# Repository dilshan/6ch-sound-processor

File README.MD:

# 5.1 channel analog audio processor

This project is a 5.1-channel, analog audio processor based on *PT2322* and [Arduino Nano](https://store.arduino.cc/products/arduino-nano).

[*PT2322*](https://www.alldatasheet.com/datasheet-pdf/pdf/167269/ETC1/PT2322.html) is an inexpensive analog audio processor introduced by [*Princeton Technology Corporation*](http://www.princeton.com.tw/). It contains 6-channel individual channel attenuators, a 3-way tone control system for front-end speakers, and a 3D audio simulation system.

In this design, we combine *PT2322* with *Arduino Nano* and interface it with PC/embedded computing boards through a USB port. Native *GTK* UI application provides to control all functions of the *PT2322* IC.

This audio processing module is an open-source hardware project. All the design files, source codes, and compiled binaries are available in this repository.

- [6ch-sound-fx-arduino](https://github.com/dilshan/6ch-sound-processor/tree/main/6ch-sound-fx-arduino): Source code of the *Arduino Nano* firmware.
- [6ch-sound-fx-controller](https://github.com/dilshan/6ch-sound-processor/tree/main/6ch-sound-fx-controller): Source code of the sound processor control application.
- [kicad-design](https://github.com/dilshan/6ch-sound-processor/tree/main/kicad-design): *KiCAD* 6 schematic and PCB design.

## Assembling the module

The PCB of this module can directly order from the [PCBWay project page](https://www.pcbway.com/project/shareproject/5_1_channel_analog_audio_processor_231ad745.html). Also, the latest Gerber files of this module are available in the [release](https://github.com/dilshan/6ch-sound-processor/releases) section of this repository.

All the required components to assemble this module are in the BOM file at [here](https://github.com/dilshan/6ch-sound-processor/tree/main/kicad-design/6ch-sound-fx-proc-bom.pdf).

The entire assembly process of this module is shown in the below video:

## Compiling source codes

*Arduino Nano* firmware of this project is written using [*PlatformIO*](https://platformio.org/). To compile and install the firmware, use the latest version of [*PlatformIO IDE*](https://platformio.org/platformio-ide).

The sound processor control application is a *GTK* application. *GTK* 3 development packages are required to compile this application. To compile the application, issue the `make` command from the source directory.

```
$ git clone git@github.com:dilshan/6ch-sound-processor.git
$ cd 6ch-sound-processor/6ch-sound-fx-controller/
$ make
```

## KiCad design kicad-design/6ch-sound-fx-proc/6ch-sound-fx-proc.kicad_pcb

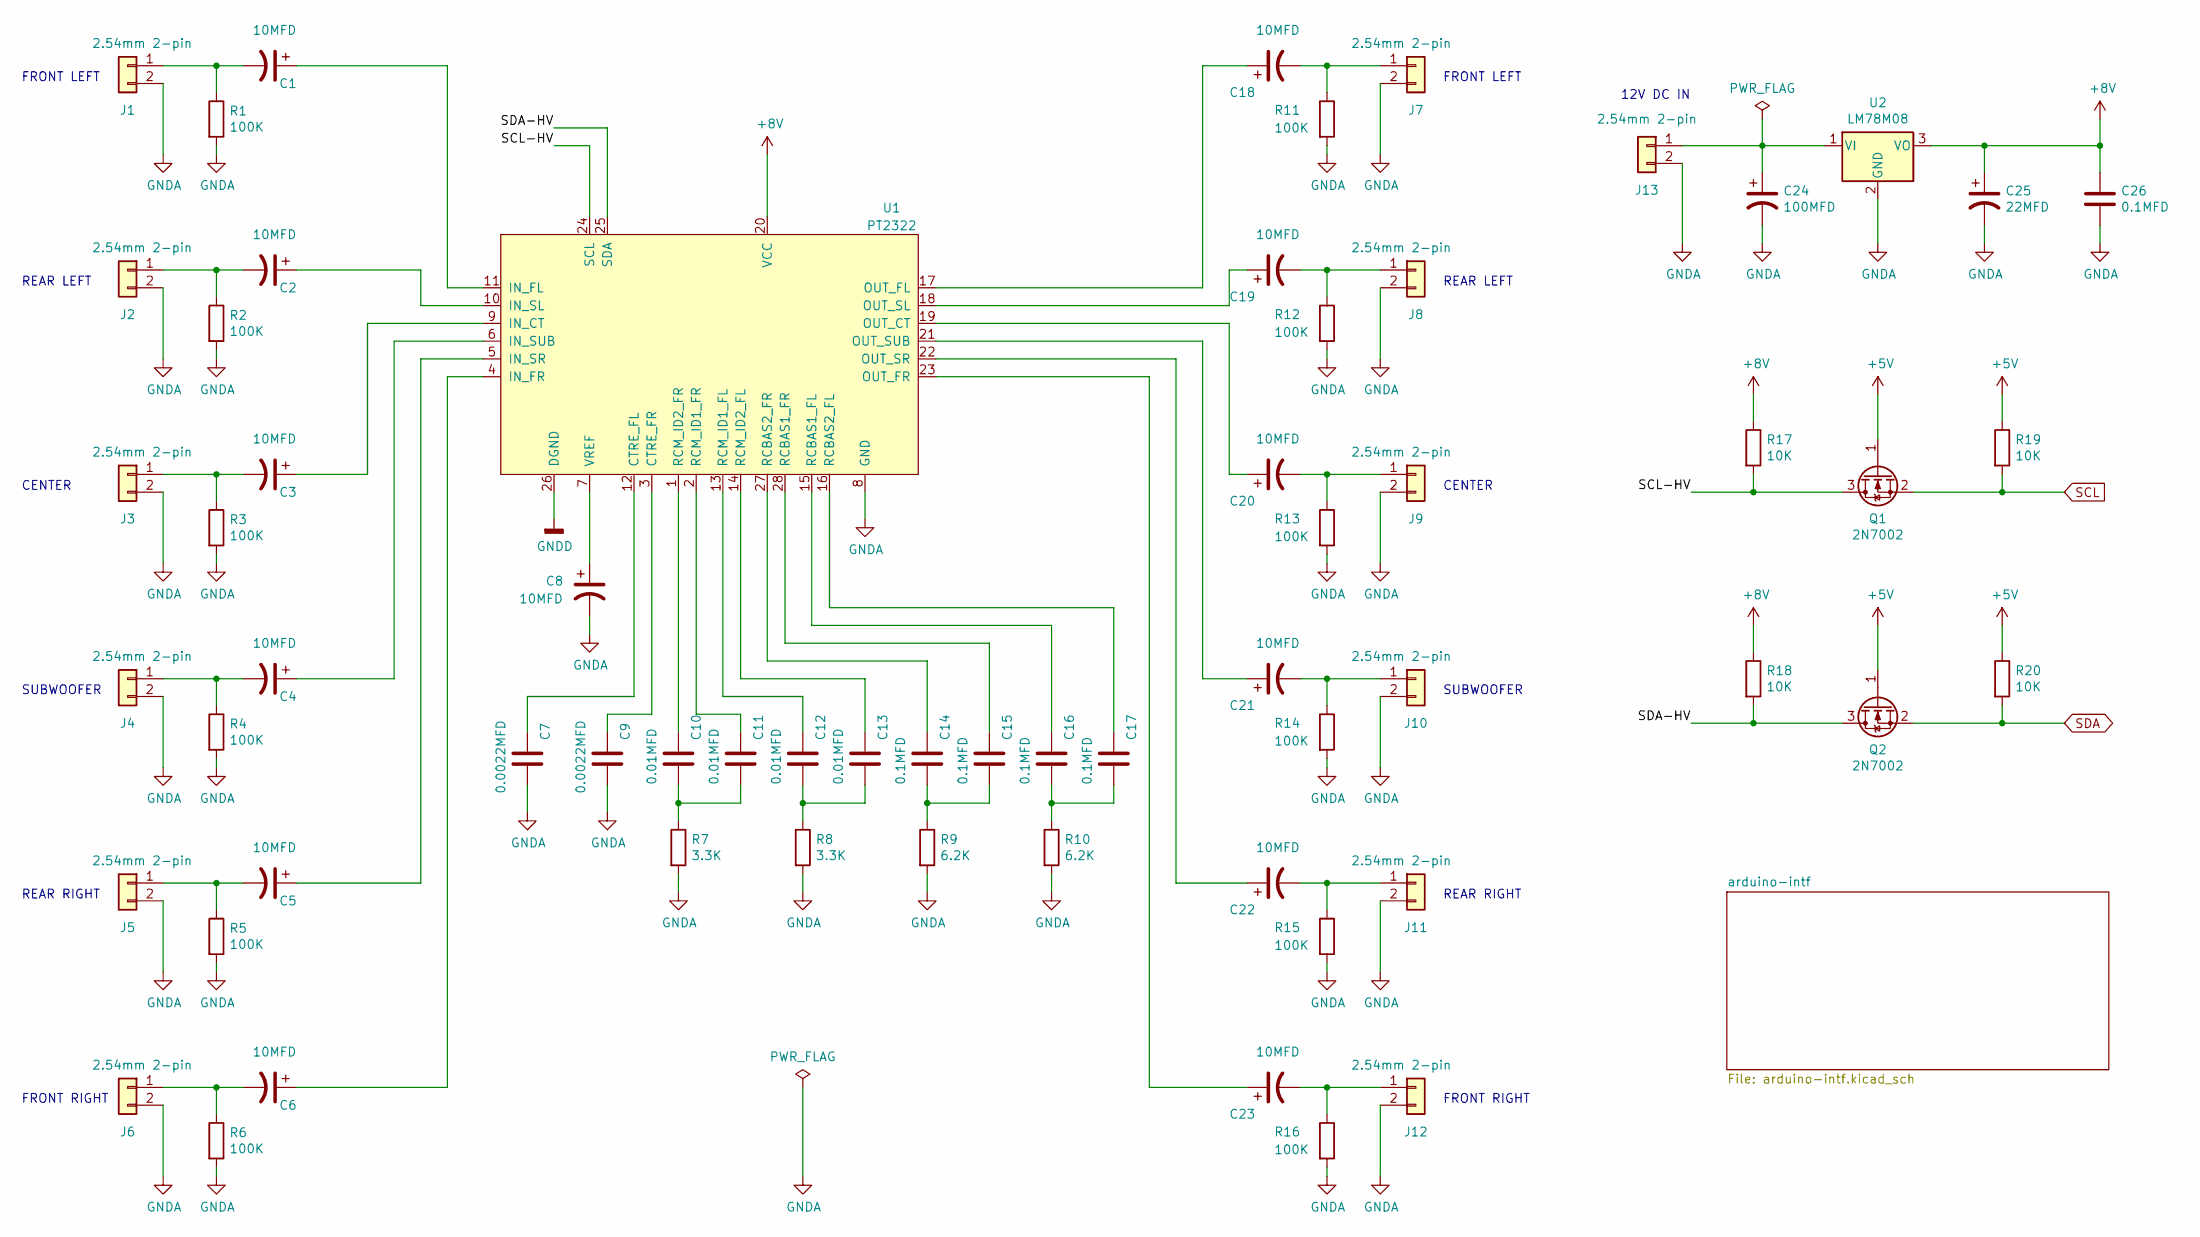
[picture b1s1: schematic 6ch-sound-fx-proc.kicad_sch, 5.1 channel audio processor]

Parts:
C1, C2, C3, C4, C5, C6, C8, C18, C19, C20, C21, C22, C23: 10MFD; CP_Radial_D5.0mm_P2.00mm
C7, C9: 0.0022MFD; C_0805_2012Metric_Pad1.18x1.45mm_HandSolder
C10, C11, C12, C13: 0.01MFD; C_0805_2012Metric_Pad1.18x1.45mm_HandSolder
C14, C15, C16, C17, C26: 0.1MFD; C_0805_2012Metric_Pad1.18x1.45mm_HandSolder
C24: 100MFD; CP_Radial_D6.3mm_P2.50mm
C25: 22MFD; CP_Radial_D5.0mm_P2.00mm
J1, J2, J3, J4, J5, J6, J7, J8, J9, J10, J11, J12: 2.54mm 2-pin; PinHeader_1x02_P2.54mm_Vertical
J13: 2.54mm 2-pin; PhoenixContact_MCV_1,5_2-G-3.5_1x02_P3.50mm_Vertical
Q1, Q2: 2N7002; SOT-23
R1, R2, R3, R4, R5, R6, R11, R12, R13, R14, R15, R16: 100K; R_0805_2012Metric_Pad1.20x1.40mm_HandSolder
R7, R8: 3.3K; R_Axial_DIN0207_L6.3mm_D2.5mm_P10.16mm_Horizontal
R9, R10: 6.2K; R_Axial_DIN0207_L6.3mm_D2.5mm_P10.16mm_Horizontal
R17, R18, R19, R20: 10K; R_0805_2012Metric_Pad1.20x1.40mm_HandSolder
U1: PT2322; SSOP-28_5.3x10.2mm_P0.65mm
U2: LM78M08; TO-252-2

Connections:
+5V: Q1.1 (G), Q2.1 (G), R19.1, R20.1; also elsewhere on the board
+8V: C25.1, C26.1, R17.1, R18.1, U1.20 (VCC), U2.3 (VO)
/SCL-HV: Q1.3 (D), R17.2, U1.24 (SCL)
/SDA-HV: Q2.3 (D), R18.2, U1.25 (SDA)
GNDA: C7.2, C8.2, C9.2, C24.2, C25.2, C26.2, J1.2, J2.2, J3.2, J4.2, J5.2, J6.2, J7.2, J8.2, J9.2, J10.2, J11.2, J12.2, J13.2, R1.2, R2.2, R3.2, R4.2, R5.2, R6.2, R7.2, R8.2, R9.2, R10.2, R11.2, R12.2, R13.2, R14.2, R15.2, R16.2, U1.8 (GND), U2.2 (GND); also elsewhere on the board
GNDD: U1.26 (DGND); also elsewhere on the board
unnamed: C1.1, U1.11 (IN_FL)
unnamed: C1.2, J1.1, R1.1
unnamed: C2.1, U1.10 (IN_SL)
unnamed: C2.2, J2.1, R2.1
unnamed: C3.1, U1.9 (IN_CT)
unnamed: C3.2, J3.1, R3.1
unnamed: C4.1, U1.6 (IN_SUB)
unnamed: C4.2, J4.1, R4.1
unnamed: C5.1, U1.5 (IN_SR)
unnamed: C5.2, J5.1, R5.1
unnamed: C6.1, U1.4 (IN_FR)
unnamed: C6.2, J6.1, R6.1
unnamed: C7.1, U1.12 (CTRE_FL)
unnamed: C8.1, U1.7 (VREF)
unnamed: C9.1, U1.3 (CTRE_FR)
unnamed: C10.1, U1.1 (RCM_ID2_FR)
unnamed: C10.2, C11.2, R7.1
unnamed: C11.1, U1.2 (RCM_ID1_FR)
unnamed: C12.1, U1.13 (RCM_ID1_FL)
unnamed: C12.2, C13.2, R8.1
unnamed: C13.1, U1.14 (RCM_ID2_FL)
unnamed: C14.1, U1.27 (RCBAS2_FR)
unnamed: C14.2, C15.2, R9.1
unnamed: C15.1, U1.28 (RCBAS1_FR)
unnamed: C16.1, U1.15 (RCBAS1_FL)
unnamed: C16.2, C17.2, R10.1
unnamed: C17.1, U1.16 (RCBAS2_FL)
unnamed: C18.1, U1.17 (OUT_FL)
unnamed: C18.2, J7.1, R11.1
unnamed: C19.1, U1.18 (OUT_SL)
unnamed: C19.2, J8.1, R12.1
unnamed: C20.1, U1.19 (OUT_CT)
unnamed: C20.2, J9.1, R13.1
unnamed: C21.1, U1.21 (OUT_SUB)
unnamed: C21.2, J10.1, R14.1
unnamed: C22.1, U1.22 (OUT_SR)
unnamed: C22.2, J11.1, R15.1
unnamed: C23.1, U1.23 (OUT_FR)
unnamed: C23.2, J12.1, R16.1
unnamed: C24.1, J13.1, U2.1 (VI)
SCL: Q1.2 (S), R19.2; also elsewhere on the board
SDA: Q2.2 (S), R20.2; also elsewhere on the board

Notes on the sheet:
SUBWOOFER
FRONT LEFT
FRONT RIGHT
REAR LEFT
REAR RIGHT
CENTER
12V DC IN

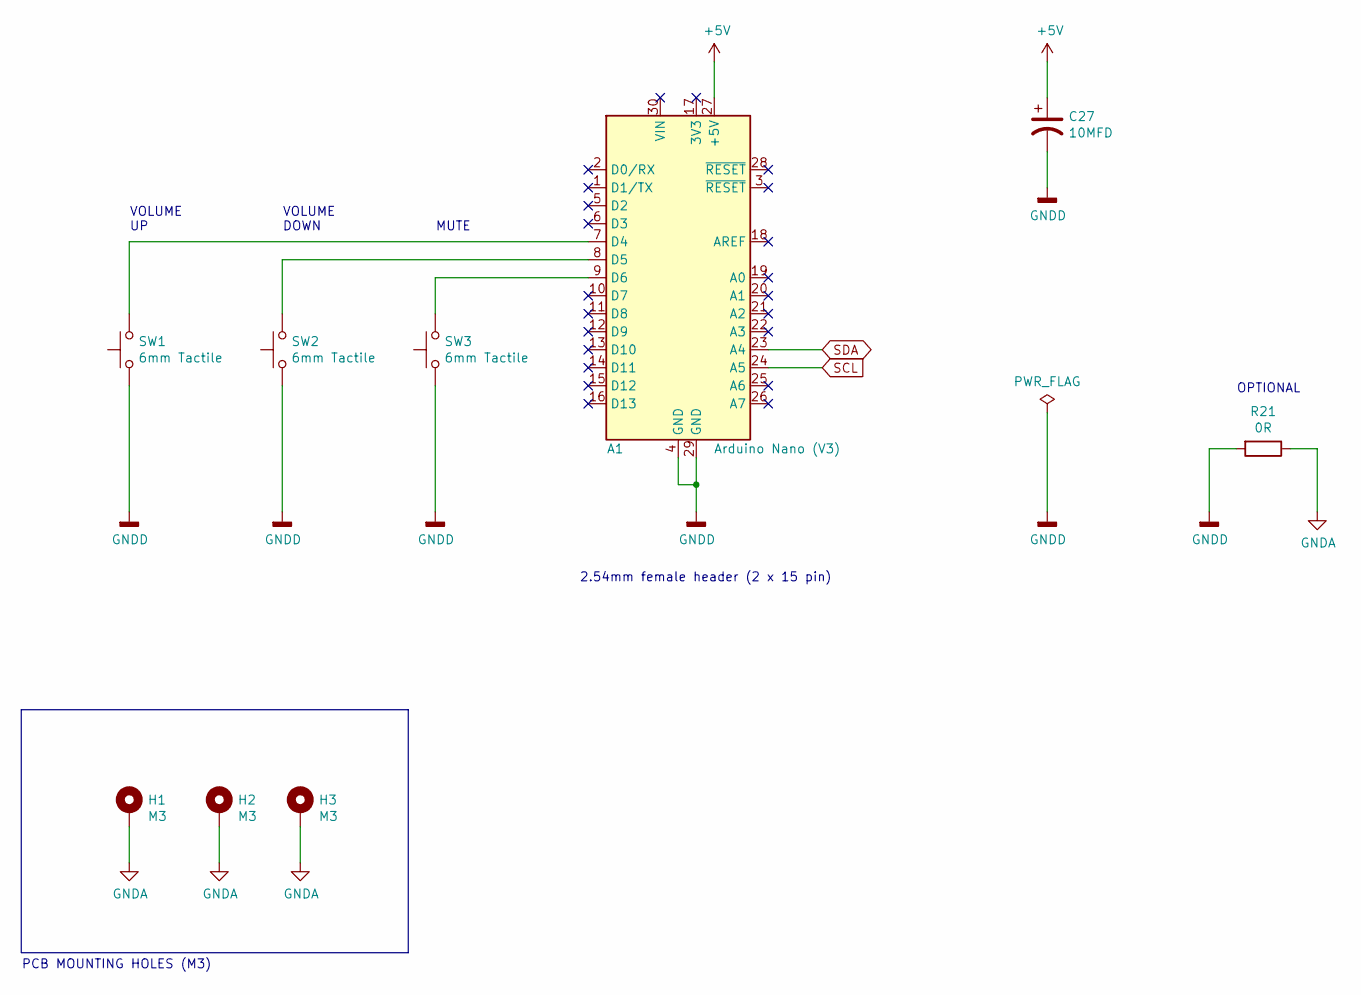
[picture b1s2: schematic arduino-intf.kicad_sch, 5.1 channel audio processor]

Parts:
A1: Arduino Nano (V3); Arduino_Nano
C27: 10MFD; CP_Radial_D5.0mm_P2.00mm
H1, H2, H3: M3; MountingHole_3.2mm_M3_Pad
R21: 0R; R_0805_2012Metric_Pad1.20x1.40mm_HandSolder
SW1, SW2, SW3: 6mm Tactile; SW_PUSH_6mm

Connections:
+5V: A1.27 (+5V), C27.1; also elsewhere on the board
GNDA: H1.1, H2.1, H3.1, R21.1; also elsewhere on the board
GNDD: A1.4 (GND), A1.29 (GND), C27.2, R21.2, SW1.1, SW2.1, SW3.1; also elsewhere on the board
unnamed: A1.7 (D4), SW1.2
unnamed: A1.8 (D5), SW2.2
unnamed: A1.9 (D6), SW3.2
SCL: A1.24 (A5); also elsewhere on the board
SDA: A1.23 (A4); also elsewhere on the board

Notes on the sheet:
2.54mm female header (2 x 15 pin)
VOLUME DOWN
PCB MOUNTING HOLES (M3)
VOLUME UP
OPTIONAL
MUTE

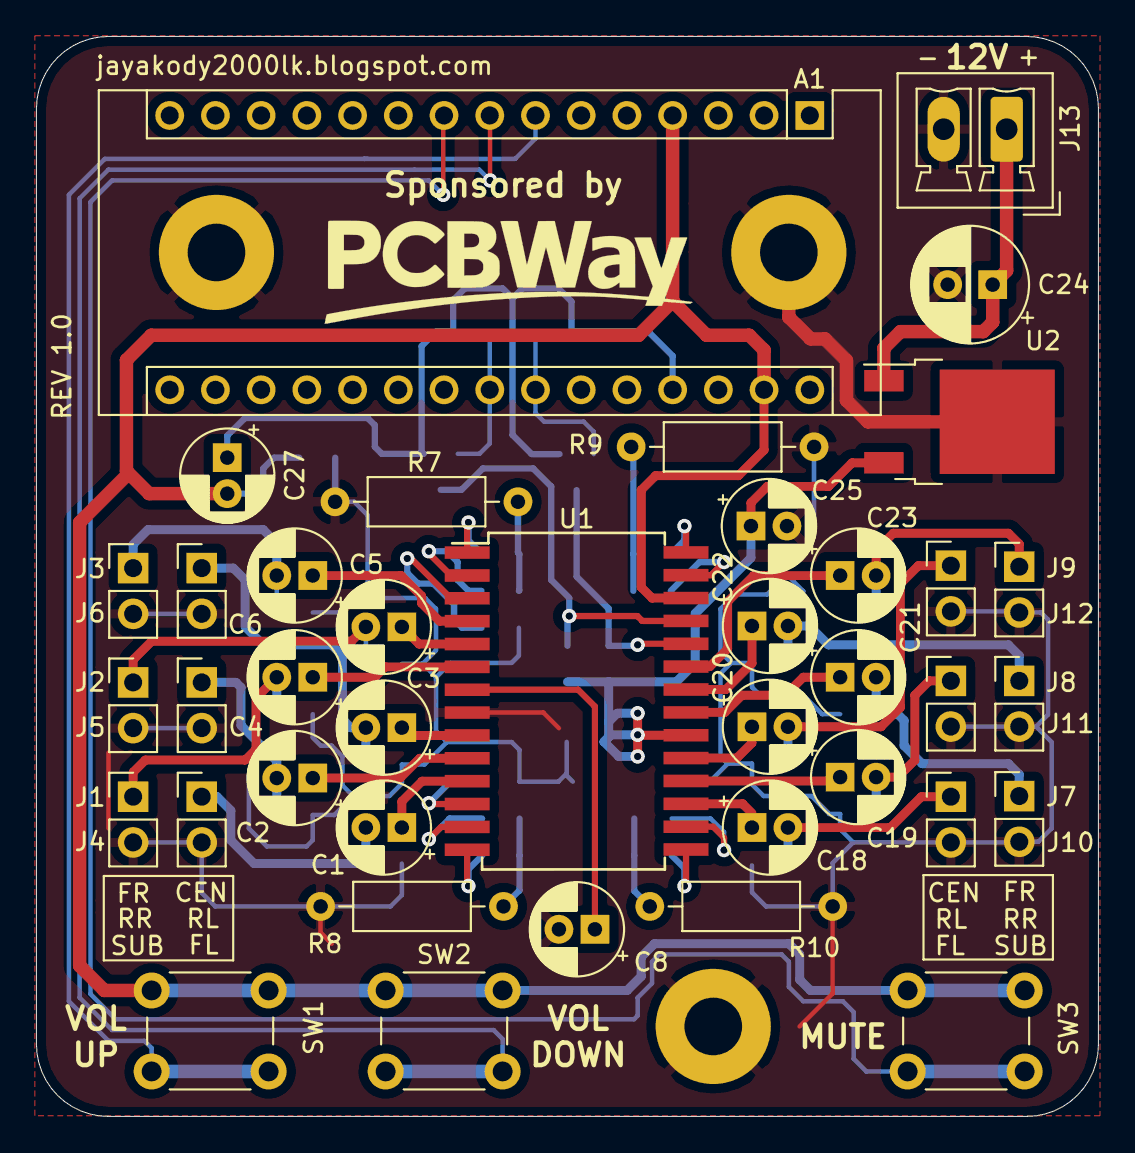
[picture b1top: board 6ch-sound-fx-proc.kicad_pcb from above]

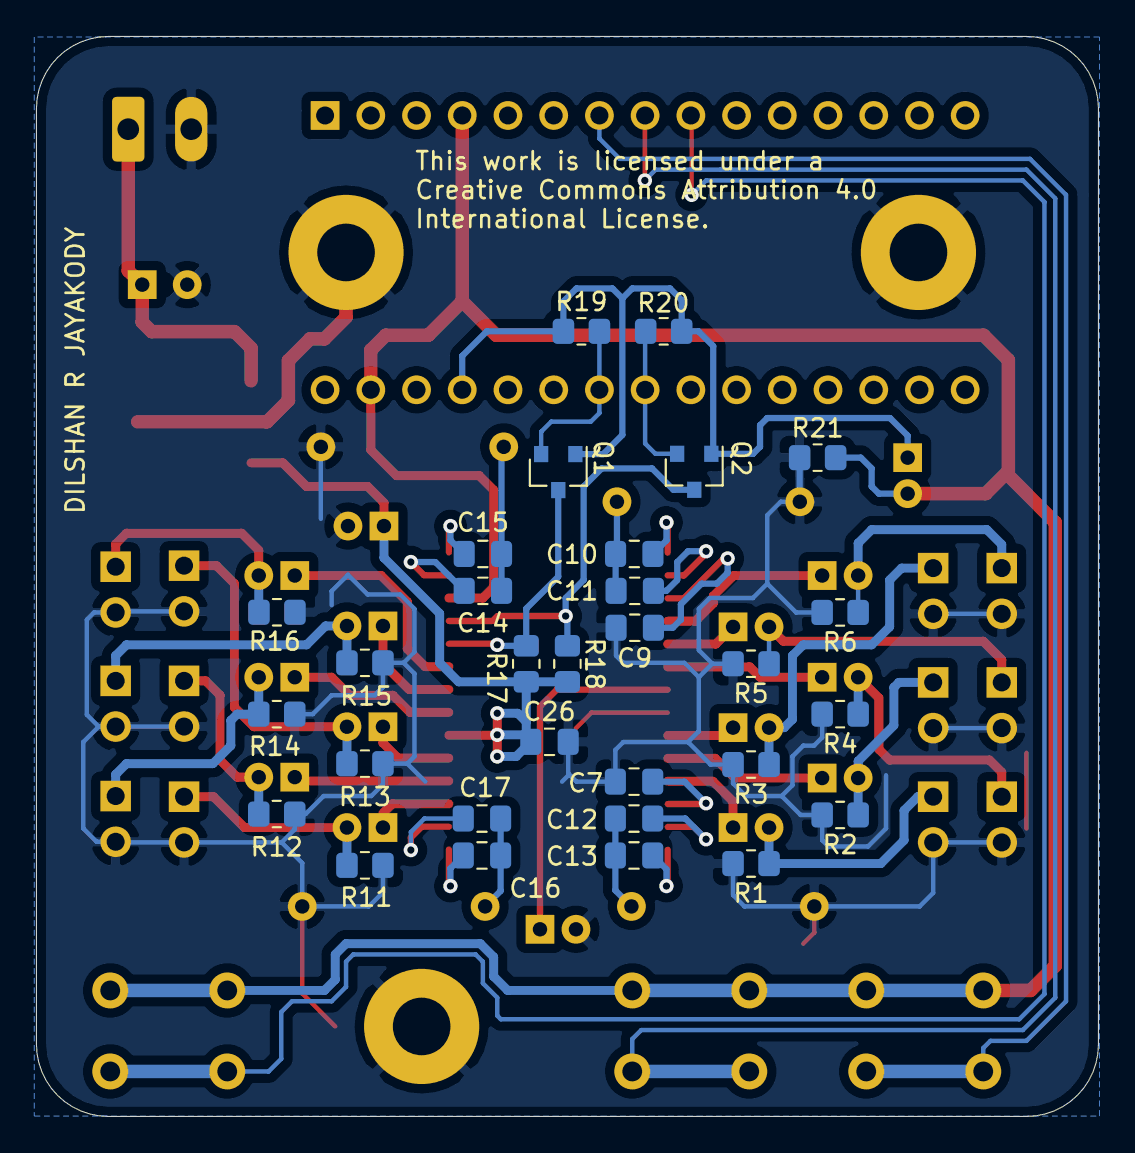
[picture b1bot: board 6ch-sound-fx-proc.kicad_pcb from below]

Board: 2 copper layers, 59.0 x 60.0 mm, 72 parts (30 on the bottom side), 51 nets.

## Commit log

2022-10-21 Add software license file.
2022-10-21 Initial commit of source files and design files.
2022-10-21 Add missing resource definition file.
2022-10-24 Update version information of the schematic and PCB design.
2022-10-24 Add BOM file and readme.md file.
2022-10-24 Add PDF version of the schematic.
2022-10-24 Add image of the prototype project and application screenshot.
2022-10-24 Update resolution of the assembled PCB image.
2022-10-24 Add board and application images to the readme.md file.
2022-10-24 Change BOM file name.
2022-10-24 Fix compilation issues with GCC 9.3.
2022-10-24 Fix UI issues in serial connection path.
2022-10-24 Add YouTube video link to the readme.md file.
2022-10-24 Add PCBWay project page URL.

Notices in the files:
kicad-design/6ch-sound-fx-proc/6ch-sound-fx-proc.kicad_pcb:
This work is licensed under a
Creative Commons Attribution 4.0
